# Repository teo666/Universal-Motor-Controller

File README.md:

# What Universal-Motor-Controller is

Universal-Motor-Controller (UMC) is an Arduino based software and hardware intended to drive universal brushed motor, like many circuit based on TDA1085.

# Main components

UMC consist of two parts:
- software: a C/C++ code running on Atmel Atmega-328p (Arduino Uno and compatibles boards)
- hardware: divided in three parts
    - zero crossing detector circuit (zcd), used for synchronize Arduino on main power
    - power circuit, used for feed motor
    - feedback circuit, used for monitoring the speed of the motor and adjust feed power consequently

# Working principle

Image below shows UMC's working diagram

- The main power is connected to zero crossing detector circuit that transform sine wave signal to a square wave signal and send it to IC, main power source is conneted to motor power switching circuit
- IC is an Atmega-328p
- the power switching circuit is for made up of a triac, it controls the power of the motor and it is drived by IC
- the tacho is the feedback circuit of the system, it generate a signal to IC in relation to motor speed.

The main target of the driver is to changes power feeding the motor to prevent slowdowns when the load changes, to achieve this goal IC analyzes signal coming from tachogenerator and consequntly it swiches triac.

For a correct switching, IC has to know the exact phase of main power source, this is guarantee by ZCD circuit.

ZCD generates a square wave with a doubled frequency compared to main power source frequency, in my case, considering a 50Hz main frequency it generate a square wave of 100Hz.
This signal is connected to a special pin of the Atmega that is able to recognize the rising edge of ZCD output signal and rise a hardware interrupt that freeze the current program execution flow and execute a special routine. This mechanism allow to the Atmega to know when the main power source has reached the value of 0 volt so that it can syncronyze the motor power circuit.

(For a more comprensive and detailed guide about triac working principle read https://en.wikipedia.org/wiki/Thyristor and https://en.wikipedia.org/wiki/TRIAC)

The above simple mechanism is enough to drive motors and it allows to change their speed with a potentiometer, for example we could read an analog value and map it along the time interval punctuated by two rising edge coming from ZCD circuit, and switch triac in relation to that value. The figure below illustrate that mechanism

Suppose to have a potentiometer to adjust the motor power: if potentiometer is turned to left the motor power decrease otherwise it increase. To achive that we have to change the switching point of triac inside main power source half period. In our case the potentiometer is connected to one of the avr analog input pin and readed value from potentiometer is mapped into a value between 0 and 999, and assume that we divide the semiperiord in 999 slice with the same width going from 0 to 999.

Now, if the potentiometer read value is 0 we want the mimimun motor power so we have to leave triac turned off.
If potentiometer get a value of 999 the desire power is maximum, we have to excite trigger immidiatly after the 0 volt point, or equivalentemente at 0th slice.
For any other value of potentiometer we have to trigger triac at slice numbered as (999 - pot_value) where pot_value is the value readed from potentiometer.

At this point the main question is: how divide half period into equal slices to know when turn on triac?
The response is: with timers.

Basically timers are hardware device enclosed into many ICs (avrs too) that can be used to count time. Think about timer like an unsigned variable going from 0 to a max value, and its content is increased by one (or decreased by one, or set to zero) every time that something happen, the something that happens is the clock signal, eventually scaled by a constant. Hardware can be configured to execute some special code (exactly like interrupt mechanism previously described) each time timer value reaches a special value, for example its maximum value.

The Atmega-328p (like arduino) is usually clocked with a 16MHz crystal oscillator, suppose to scale the clock with a 128 factor and use that signal to feed a 8bit timer. With that configuration timer increase its value by one every 
1 / (16e6 / 128) = 0.000008 seconds or 8 microseconds, and suppose to configure hardware to execute the special code (called Interrupt Service Routine or ISR) every time timer reach maximum value that in a 8bit configuration is 255, and the ISR increase the `tick_count` variable value by one starting from 0.

After 256 * 8 = 2048 microseconds `tick_count` value is incresed to 1  
After 4096 microsecond `tick_count` value is 2  
After 6144 microsecond `tick_count` value is 3  
After 8192 microsecond `tick_count` value is 4  
...  
After 999424 microseconds `tick_count` value is 488

or equivalently, when `tick_count` is 488 approximately a seconds is passed, that is how Arduino libraries implements millis, micros and delay functions.

The idea that we use is the same: increase a variable by one periodically inside the timer's overflow ISR (executed when timer reaches its maximum value) and reset it when ZCD find a zero volt point... then reapeat.

Go back to potentiometer example. Suppose to be immediatly after a 0 volt point and ZCD has reset our variable, and also use following condition to turn on triac.

``` c++
if( tick_count >= (999 - pot_value)){
    turn_on_triac();
}
```
- if potentiometer is set to maximum value (999) then (999 - pot_value) = 0, our variable is greater or equal to 0 and the triac is turned on
- if potentiometer is set to minimum value (0) then (999 - pot_value) = 999, our variable is less than 999 and the triac remains off
- likewise intermediate values

when next 0 volt poin occur, ZCD interrupt is executed, the `tick_count` variable is reset, and the process is repeated.

At this point we have a mixture of software and hardware that is commoly called *dimmer*, a device that can change power given to a load turning a potentiometer, those kind of devices are usually used to change halogen lamps brightness, the next step is feedback circuit integration.

The feedback circuit allow system to react to load changes and increase motor power to avoid slowdowns. The feedback circuit receives a signal coming from the tachogenerator of the motor, make some process on it and send it to IC.
The tachogenerator signal is commonly an AC sine wave signal that increase its frequency and voltage as the speed increases, so it is possible use frequency or voltage or event both together to analyze the speed of the motor, in UMC frequency is used.
The tacho AC signal is converted to an AC square wave signal and then only the positive component is taken, giving to IC a DC square wave signal. The figure below show the tacho processing signal

Once IC receives the feedback signal it has to get its frequency to know the actual speed motor and change its power consequently. To do that UMC use the same tecnique used for ZCD: interrupt mechanism.

Each time feedback signal goes from low to high (rising edge) IC's hardware generates an interrupt, the normal code execution is paused and associated ISR is executed.  
Previously we have talked about measuring signal frequency, in truth we do not need know the exact frequency, instead just a value related to frequency on wich make a comparison.  
At this point is relatively simple to get an evaluation of feedback signal frequency. Do you remember the use of timer for periodically check if triac has to be turned on? Ok, we use the same routine for increase a counter associated to feedback signal and we will reset that value in ISR associated to feedback rising edge event. In that manner we have a value related to frequency: the higher the frequency (motor speed) the lower is the couter.

At this point IC has all needed parameter for controlling power motor, and for do that we use a PID controller, you can read more about PID controller on [Wikipedia](https://en.wikipedia.org/wiki/PID_controller), about 
[used library](https://playground.arduino.cc/Code/PIDLibrary) and 
[detailed library explanation](http://brettbeauregard.com/blog/2011/04/improving-the-beginners-pid-introduction/).

# Hardware
DISCLAIMER: I am not a electrical engineer and all these circuits were taken on web and put together with a limited knowledge of them. If you have suggest to improve them and UMC you are welcome.

Below are reported the schematic circuits used in UMC
### Zero crossing detector circuit

note: VCC is 5 volt, all resistor are 1/4 watt,T1 and OK1 can be changed with equivalent components.  
PORTD,PIN2 is equivalent to pin 2 on Arduino-UNO board

### Motor power circuit

note: all resisor are 1/4 watt except R8 that is 1 watt (instead one 100 ohm resistor i recilced four 470 ohm resistor in parallel) , C3 must have appropriate galvanic isolation, for T2 I used a BTB16 couse BT138 gave me some problem.  

PORTD,PIN7 is equivalent to pin 7 on Arduino-UNO board

note: zcd and motor power circuits on same pcb

### Feedback circuit

note: note: all resisor are 1/4 watt, Vcc is 9 volts, IC1 can be replaced with another opamp  

PORTD,PIN3 is equivalent to pin 3 on Arduino-UNO board

this board contains the potentiometer connector too and a push button connected to PORTD,PIN6 that is equivalent to pin 6 on Arduino-UNO board. We will talk about the push button later.

All together

### Motor connection

Usually universal motor has six cable:
- two for the rotor
- two for the stator
- two for the tachogenerator

The cables of tachogenerator have to be connected to the tacho circuit and the order is irrilevant.  
The rotor and stator windings have to be connected in series togheter with main AC power source and power circuit, as show below.  
**NOTE: swap stator terminals to change rotation direction of the motor.**

### UMC box

This photo show UMC with its box, taken from an old ATX power supply

### Demo video

This [video](https://youtu.be/NKULTa6kquY) is a demonstration about UMC capabilities.  
This [video](https://youtu.be/l1mFbbu4X3Q) show capabilities of UMC on low speed.  
These two [video1](https://youtu.be/YVdLVX_Wkz4) and [video2](https://youtu.be/LLw0HUfIIPY) show a motor driven by UMC connected to a bench grindstone disconnected from main power.  
This [video](https://youtu.be/WyjBL2rSP_o) show UMC with current measurement.
# Speed limiter

UMC comes with a spftearec based speed limiter. Speed limiter use the feedback signal to to achive this goal. Speed limiter is usefull because it allow to map all potentiometer turning range inside the desired motor speed limits.  
In some application we could need maximum motor speed around 2000 rmp and in other 4000 rmp, but we want reach those speed when potentiometer is completely at the most, and leave hardware and software as they are, without needs of modifications.
At the moment it is possible limit the speed only during avr's boot process using the *programming button*.
Programming Button is a push button that if pressed connect PORTD,PIN6 (pin 6 of Arduino Uno) to ground, and allow us to set limit speed values (low and high), these values are stored in avr's EEPROM so they are accessible at the next restart, whitout needs to set up them every time.

**CAUTION: programming button is used to switch from automatic to manual mode too. Manual mode allow to disable the feedback circuit and use UMC as a simple dimmer. Suppose to have upper speed limit set to 1000 rpm and runnign motor with this speed, so with potentiometer at maximum. If you press programming button in this condition the motor will receice all possible power and its speed will increase with possible motor or equipment damage.**

### Usage

- Connect Arduino to PC, on Arduino IDE open serial monitor (ensure all parameter are correct: serial port, board etc)
- press and hold the *programming button*
- reset the board keeping *programming button* pressed
- read serial monitor keeping *programming button* pressed and follow printed instructions

At the end of process if you turn potentiometer the speed motor is limeted inside selected range.

# Configuration

Attention: before reading this section be sure that you know what PID parameters are, otherwise follow links at the end of "Working principle" section.

With 1.0.1 version UMC comes with dynamic PID parameter change. Basically UMC can change its PID parameter in relation to motor speed, in fact some parameters that work correctly at a fixed speed can be wrong at lower or higher speed, making UMC non-reactive or causing rotation spikes.  
To achive this gol the constructor of PID library take extra parameters, such as a function, that it is called inside `compute()` PID function to get the correct PID parameters.
That function is named `search` and it is placed inside `configuration.h` file. You have to customize `search` function to satisfy your preferences.
The signature of `search` function is the following
``` c++
CoefficientPtr search() {
    ...
}
```
it must return a `CoefficientPtr` that is define in `PID_ASYNC.h` as
``` c++
typedef struct _coefficient {
  double Kp;
  double Ki;
  double Kd;
} Coefficient;

typedef Coefficient *CoefficientPtr;
```
Inside `configuration.h` file you can find an example of search function that meets my needs, the code is the following
``` c++
//static parameter declaration
Coefficient k_param[9];

/**
* function called inside setup() to fetch parameter
*/
void init_params() {
  k_param[0].Kp = 0.3;
  k_param[0].Ki = 0.0001;
  k_param[0].Kd = 0;

  k_param[1].Kp = 0.8;
  k_param[1].Ki = 0.0001;
  k_param[1].Kd = 0;

  k_param[2].Kp = 1;
  k_param[2].Ki = 0.0001;
  k_param[2].Kd = 0;

  k_param[3].Kp = 1.5;
  k_param[3].Ki = 0.0002;
  k_param[3].Kd = 0;

  k_param[4].Kp = 2;
  k_param[4].Ki = 0.0002;
  k_param[4].Kd = 0;

  k_param[5].Kp = 3;
  k_param[5].Ki = 0.0002;
  k_param[5].Kd = 0;

  k_param[6].Kp = 3;
  k_param[6].Ki = 0.001;
  k_param[6].Kd = 0;

  k_param[7].Kp = 3;
  k_param[7].Ki = 0.001;
  k_param[7].Kd = 0;

  k_param[8].Kp = 7;
  k_param[8].Ki = 0.002;
  k_param[8].Kd = 0;
}

/**
 * function called inside compute() PID function
 * get the minimum value from Setpoint and Input 
 * and use it to chose the correct parameters
 */
CoefficientPtr search() {
  double _val = min(Setpoint, Input);
  uint8_t index = 0;

  if (_val >= 550) {
    index = 0;
  } else if (_val >= 500 && _val < 550) {
    index = 1;
  } else if (_val >= 450 && _val < 500) {
    index = 2;
  } else if (_val >= 400 && _val < 450) {
    index = 3;
  } else if (_val >= 350 && _val < 400) {
    index = 4;
  } else if (_val >= 250 && _val < 350) {
    index = 5;
  } else if (_val >= 200 && _val < 250) {
    index = 6;
  } else if (_val >= 150 && _val < 200) {
    index = 7;
  } else if (_val <= 150) {
    index = 8;
  }
  return &k_param[index];
}
```

- on the top an array is declared to hold different `Coefficient` structures,
- the method `init_params()` is declared, it allow you to initialize the array, in the above code it is initialized statically, but you could need to read some value from EEPROM and store them inside it.
- the `search` function is declared, it is responsible for providing dynamic parameters to PID in relation to the speed of the motor.

Inside `configuration.h` file you have access to all available global variables, for example Setpoint, Input and Output PID variables, but **DON'T MODIFY THEM, JUST READ THEM**.

Ok... but, where those value (500, 350 and so on) come from?  
They come from **test mode**. *test mode* allow you to run UMC, change speed with potentiometer and set dynamically PID parameters to test them with no need to flash the ROM of the avr everytime.
To use *test mode* uncomment first line in the `Universal_Motor_Controller.ino` file to get
``` c++
#define TEST_MODE
```
and then flash avr.  
Open serial monitor, current *Setpoint*, *Input* and *Output* values are shown. You can change the *kp*, *ki* and *kd* parameters in serial input, giving the command
``` bash
<param_name> <value>
```
where `param_name` can be 
``` bash
kp
ki
kd
```
to set respectively proportional, integral or derivative parameter  
and `value` is a floating point value like 
``` bash
0.0002
```
**ATTENTION: THERE IS ONLY ONE SPACE BERTWEEN TWO ARGUMENTS** 

**ATTENTION: PARAMETERS MUST BE GIVEN SEPARATELY, YOU CAN'T SET THEM ALL TOGHETER, ONLY ONE BY ONE**  

**ATTENTION: K-VALUES ARE SHOWN WITH EIGHT DECIMAL DIGIT PRECISION**

While program runs it shows current *Setpoint* and *Input* values that can be used to discriminate the correct PID weights inside *search* function, that is where previous unknow numbers come from. With these value it is possible to see how UMC react to load change, considering that *Input* value should be near as possible to *Setpoint*.

Once done you can create your own `init_params` and `search` function and comment first line into `Universal_Motor_Controller.ino` file to get
``` c++
//#define TEST_MODE
```
and flash again.

Enjoy!

# Changelog

v1.0.1
- UMC comes with its own version of PID library, it is heavily based on Brett Beauregard's PID library  
(library link:  https://playground.arduino.cc/Code/PIDLibrary  
email: <br3ttb@gmail.com>  
library explanation: http://brettbeauregard.com/blog/2011/04/improving-the-beginners-pid-introduction/): the new version is basically identical to Brett Beauregard's version except for the facts that it is now asynchronous and some unused methods are deleted.
- UMC can now change its PID parameters dynamically, related to motor speed.
- Improved motor stability on low speed
- Code revisiting.
- UMC comes now with a test mode usefull for calibration.

v1.0.2
- Improved initial frequency calculation by decreasing needed time
- Added zero crossing detection circuit fail detection condition. Before this version when a zcd circuit fail occur UMC gave all power to the motor
- Added motor hang/stop detection condition (early version to use with caution)
- UMC is now (partially) invulnerable to the power line frequency changes
- Added eagle project files including circuit schematic and board layout

# Known problems and Improvements

This is an early UMC version and there are many things to improve.  
I hope that someone will find this project interesting helping me (and diyers community) to improve its capabilities.

### Higher priority 
- Slow start integration (via PID controller)
- Allow rotation inversion (require hardware modification and hang/stop detection)

### Lower priority

- Lower speed limit can't be set to 0rpm.
- Program lives as it is, there isn't an Object Oriented Programming model and integrations with other libraries are difficult due to time dependent application nature.
- UMC doesn't allow connect multiple motor due low number of Atmega-328p interrupt pins. One is necessary for ZCD circuit the other for feedback circuit. I'm trying to remove this lack using a frequncy to analog converter that technically will allow drive up to six motor. Should be possible monitor feedback signal without the need of interrupt pin by checking it periodically inside timer's ISR, but I have not tested this method yet.
- OOP usage is releted to the above two problems.

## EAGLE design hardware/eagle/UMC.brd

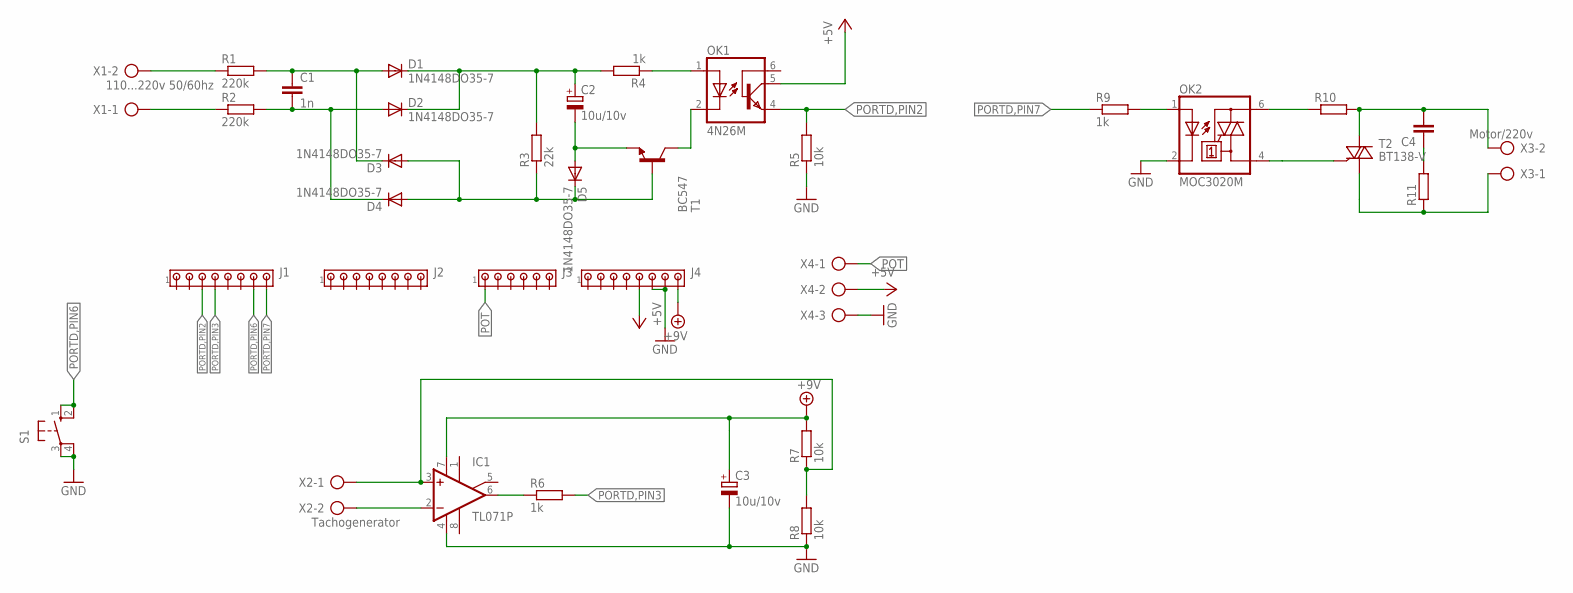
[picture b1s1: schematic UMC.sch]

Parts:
C1: 1n; C5B2.5
C2, C3: 10u/10v; E2,5-5
C4: C15/7; C15B7
D1, D2, D3, D4, D5: 1N4148DO35-7; DO35-7
IC1: TL071P; DIL08
J1, J2, J4: MTA08-100; 10X08MTA
J3: MTA06-100; 10X06MTA
OK1: 4N26M; DIL06
OK2: MOC3020M; DIL06
R1, R2: 220k; 0207/7
R3: 22k; 0207/7
R4, R6, R9: 1k; 0207/7
R5, R7, R8: 10k; 0207/7
R10: R-EU_0207/7; 0207/7
R11: R-EU_0411/12; 0411/12
S1: 10-XX; B3F-10XX
T1: BC547; TO92
T2: BT138-V; TO220BV
X1: 110...220v 50/60hz; AK500/2
X2: Tachogenerator; AK500/2
X3: Motor/220v; AK500/2
X4: AK500/3

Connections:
+5V: J4.5, OK1.5 (COL), X4.2
+9V: C3.+, IC1.7 (V+), J4.8, R7.2
GND: C3.-, IC1.4 (V-), J4.6, J4.7, OK2.2 (C), R5.1, R8.1, S1.3, S1.4 (P1), X4.3
unnamed: R1.1, X1.2
unnamed: R2.1, X1.1
unnamed: C1.1, D1.A, D3.C, R1.2
unnamed: C1.2, D2.A, D4.C, R2.2
unnamed: C2.+, D1.C, D2.C, R3.2, R4.2
unnamed: D3.A, D4.A, D5.C, R3.1, T1.2 (B)
unnamed: OK1.1 (A), R4.1
unnamed: OK1.2 (C), T1.3 (C)
unnamed: C2.-, D5.A, T1.1 (E)
unnamed: OK2.1 (A), R9.2
unnamed: IC1.2 (-IN), X2.2
unnamed: IC1.6 (OUT), R6.1
unnamed: OK2.6 (A2), R10.1
unnamed: IC1.3 (+IN), R7.1, R8.2, X2.1
unnamed: C4.2, R10.2, T2.T2 (A2), X3.2
unnamed: C4.1, R11.2
unnamed: OK2.4 (A1), T2.G
unnamed: R11.1, T2.T1 (A1), X3.1
PORTD,PIN2: J1.3, OK1.4 (EMI), R5.2
PORTD,PIN3: J1.4, R6.2
PORTD,PIN6: J1.7, S1.1 (S), S1.2 (S1)
PORTD,PIN7: J1.8, R9.1
POT: J3.1, X4.1

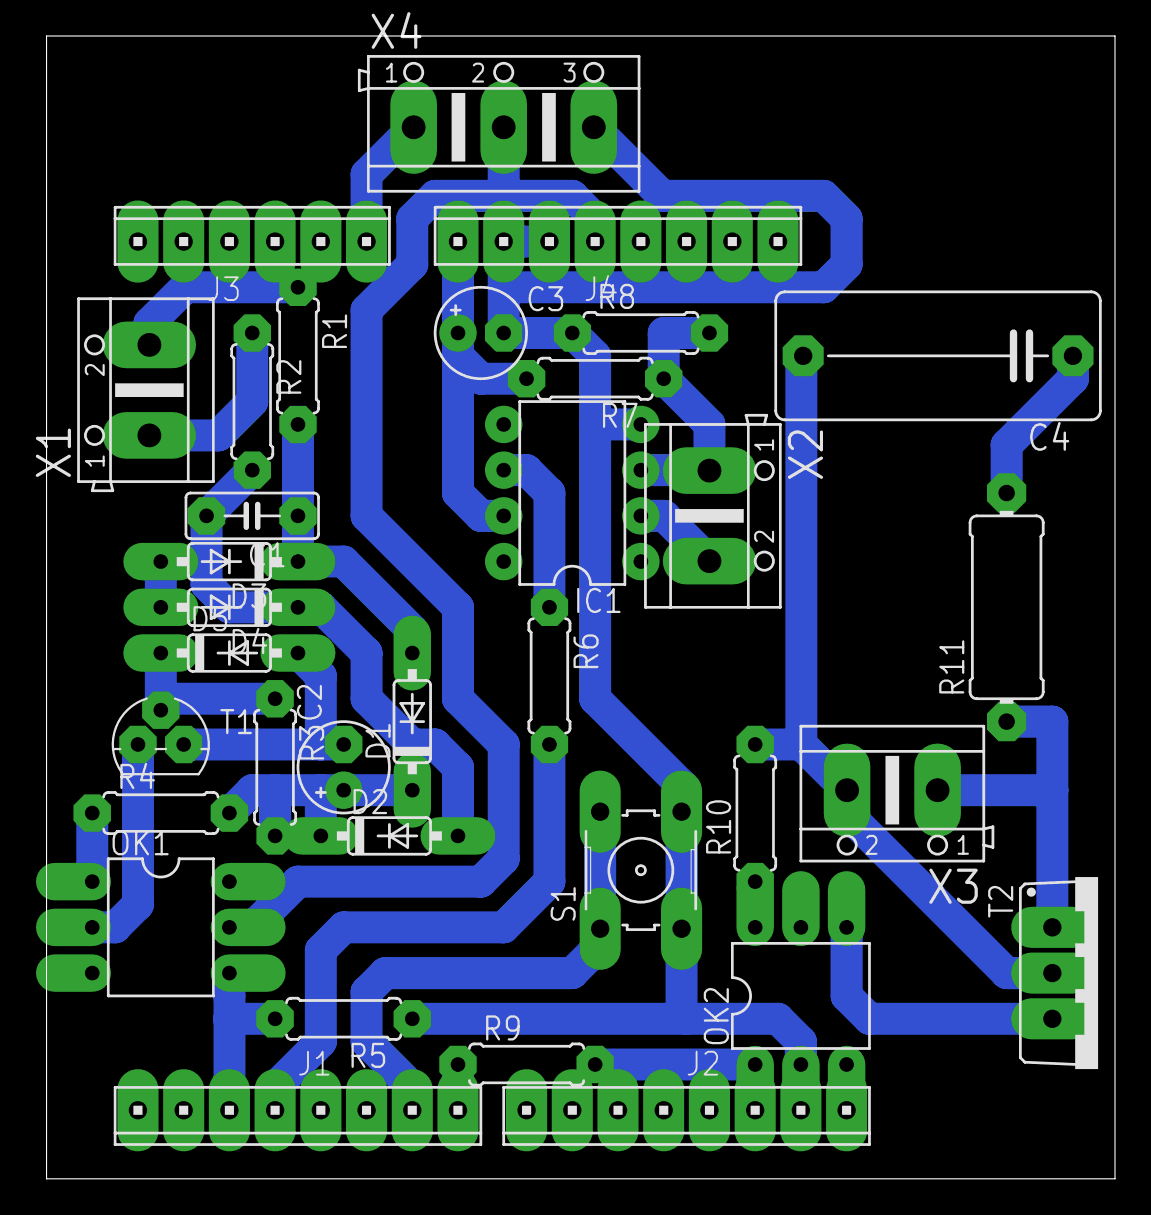
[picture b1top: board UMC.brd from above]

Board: 2 copper layers, 59.4 x 63.5 mm, 34 parts (0 on the bottom side), 26 nets.

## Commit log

2018-07-21 commit per conclusione parte di alimentazione, inizio parte feedback
2018-07-21 parte relativa all'analisi del segnale di tacho
2018-07-21 conclusione feedback versione 1
2018-07-22 fine controllo feedback rozzo, inizio integrazione con PID
2018-07-22 aggiunto controllo PID
2018-07-22 inclusine README
2018-07-22 none
2018-07-24 modifiche per prove
2018-07-24 working block
2018-07-24 readme
2018-07-25 pot img
2018-07-26 documentazione
2018-07-27 tacho
2018-07-27 tacho schematic
2018-07-27 boards
2018-07-27 niente
2018-07-28 doc video
2018-07-29 dopo il setup disabilitare la modalita manuale
2018-07-30 integrazione PID
2018-07-30 prova
2018-07-31 integrazione tabella valori pid
2018-08-03 miglioramenti vari
2018-08-03 integrazione button_hold
2018-08-03 rimozione funzione di settaggio all'interno del setup con creazione nuove funzioni separate
2018-08-03 rimozione parametri inutili
2018-08-03 pulizia codice
2018-08-03 fine pulizia codice
2018-08-03 inclusione libreria PID asincrona nel progetto stesso
2018-08-03 modifiche minori
2018-08-03 comment
2018-08-03 rimozione funzioni non utilizzate del pid
2018-08-04 change log
    -aggiunta modalita di test per provare i valori del pid
    -modificata libreria pid per renderla asincrona con il tacho
    -spostamento del codice in file separati
    -il motore risulta ora stabile anche a bassi giri (test parametri pid)
    -le funzioni per la programmazione sono state spostate e rese uniformi con il dice di callback del bottone
2018-08-07 creazione tabella valori
2018-08-08 aggiunta video
2018-08-08 changelog
2018-08-08 cambio nome
2018-08-08 correzioni errori
2018-08-12 zcd error correction
2018-08-12 correzione isr
2018-08-12 zcd fail detection
2018-08-12 -stabilita' a cambi di frequenza -rilevazione fallimenti zcd -rilevazione motore fermo -riduzione attesa iniziale
2018-08-12 abilitazione esecuzione sporadica
2018-08-30 hang detection
2018-08-30 aggiunta hang detection
2018-08-30 aggiunte modifiche versione 1.0.2
2018-08-30 aggiunta progetti eagle
2020-09-09 fix macro
2020-09-12 file rename
